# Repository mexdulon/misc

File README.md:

View this project on [CADLAB.io](https://cadlab.io/node/870). 

# misc
Miscellaneous stuff like other boards (e.g. RS485)

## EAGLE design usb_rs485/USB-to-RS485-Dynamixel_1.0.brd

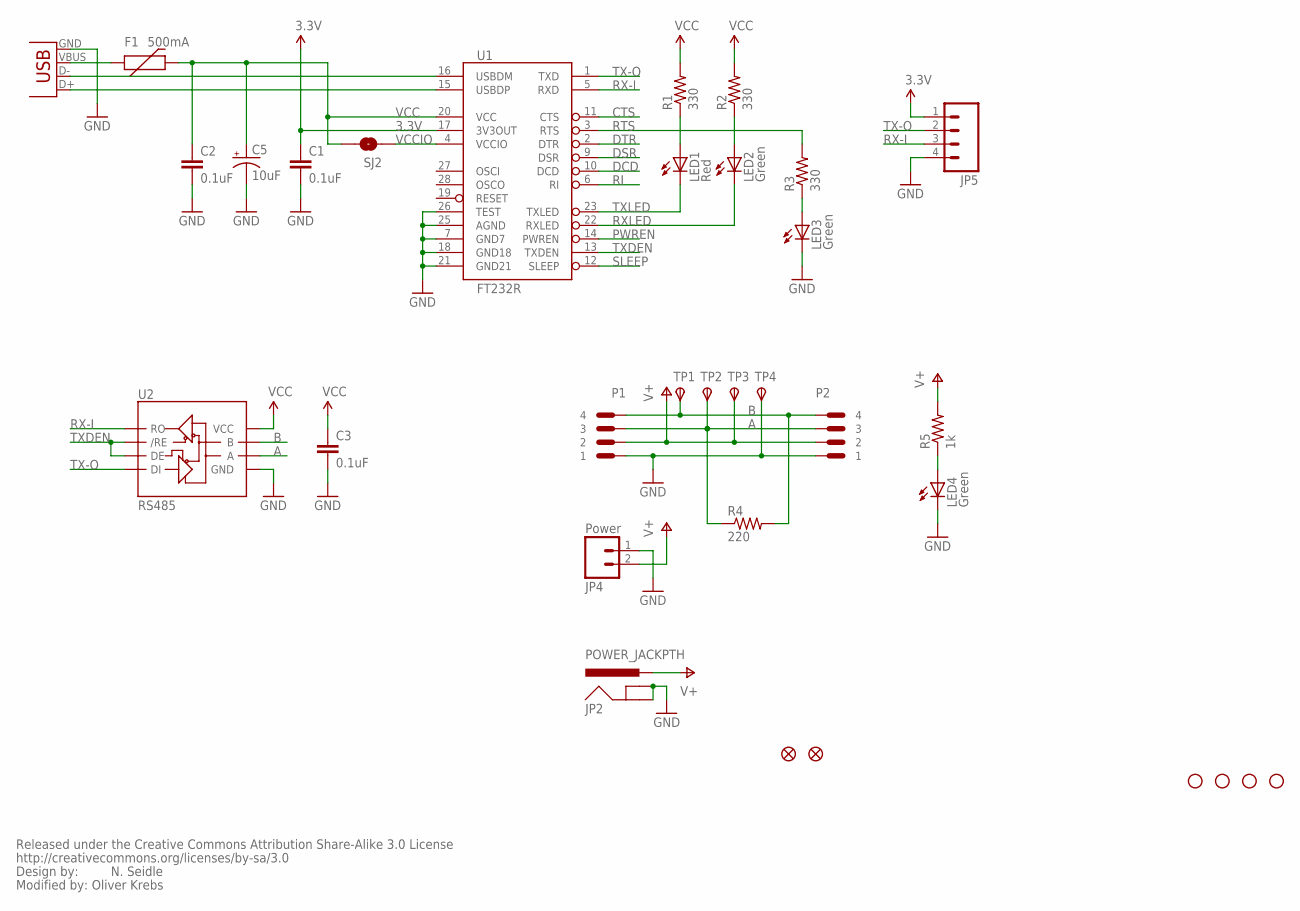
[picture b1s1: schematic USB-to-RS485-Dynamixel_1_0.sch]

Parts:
C1, C2, C3: 0.1uF; 0402-CAP
C5: 10uF; EIA3216
F1: 500mA; PTC-1206
JP1, JP6, JP7, JP8: STAND-OFF
JP2: POWER_JACKPTH; POWER_JACK_PTH
JP4: Power; 1X02_BIG_5.08
JP5: M04PTH; 1X04
JP9, JP10: FIDUCIAL1X2; FIDUCIAL-1X2
LED1: Red; LED-0603
LED2, LED3, LED4: Green; LED-0603
P1, P2: CON-4-; MOLEX-22035045
R1, R2, R3: 330; 0402-RES
R4: 220; 0402-RES
R5: 1k; 0402-RES
SJ2: SOLDERJUMPERNC2; SJ_2S-NOTRACE
TP1, TP2, TP3, TP4: TPSTP13SQ; TP13SQ
U1: FT232R; SSOP28DB
U2: RS485; SO08
U$1: CREATIVE_COMMONS
X2: USBSMD; USB-MINIB

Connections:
3.3V: C1.1, JP5.1, U1.17 (3V3OUT)
A: P1.P$3 (3), P2.P$3 (3), R4.1, TP2.TP, U2.6 (A)
B: P1.P$4 (4), P2.P$4 (4), R4.2, TP1.TP, U2.7 (B)
CTS: U1.11 (CTS)
DCD: U1.10 (DCD)
DSR: U1.9 (DSR)
DTR: U1.2 (DTR)
GND: C1.2, C2.2, C3.2, C5.C (-), JP2.GND, JP2.GNDBREAK, JP4.1, JP5.4, LED3.C, LED4.C, P1.P$1 (1), P2.P$1 (1), TP4.TP, U1.7 (GND7), U1.18 (GND18), U1.21 (GND21), U1.25 (AGND), U1.26 (TEST), U2.5 (GND), X2.GND
unnamed: LED1.A, R1.1
unnamed: LED2.A, R2.1
unnamed: F1.1, X2.VBUS
unnamed: LED3.A, R3.1
unnamed: LED4.A, R5.1
PWREN: U1.14 (PWREN)
RI: U1.6 (RI)
RTS: R3.2, U1.3 (RTS)
RX-I: JP5.3, U1.5 (RXD), U2.1 (RO)
RXLED: LED2.C, U1.22 (RXLED)
SLEEP: U1.12 (SLEEP)
TX-O: JP5.2, U1.1 (TXD), U2.4 (DI)
TXDEN: U1.13 (TXDEN), U2.2 (/RE), U2.3 (DE)
TXLED: LED1.C, U1.23 (TXLED)
USB_D+: U1.15 (USBDP), X2.D+
USB_D-: U1.16 (USBDM), X2.D-
V+: JP2.PWR, JP4.2, P1.P$2 (2), P2.P$2 (2), R5.2, TP3.TP
VCC: C2.1, C3.1, C5.A (+), F1.2, R1.2, R2.2, SJ2.2, U1.20 (VCC), U2.8 (VCC)
VCCIO: SJ2.1, U1.4 (VCCIO)

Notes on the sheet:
N. Seidle
Modified by: Oliver Krebs

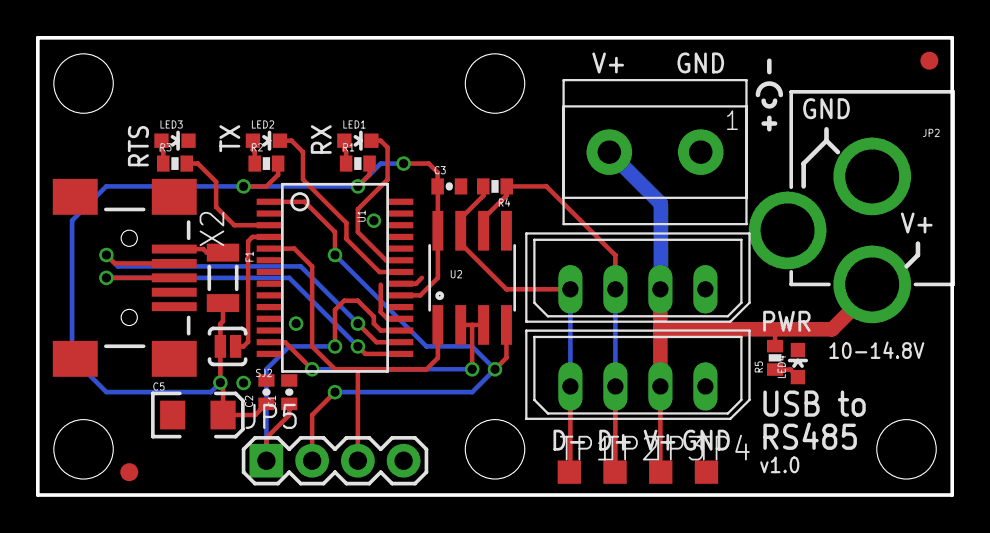
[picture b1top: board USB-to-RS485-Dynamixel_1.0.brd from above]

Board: 2 copper layers, 50.8 x 25.4 mm, 35 parts (0 on the bottom side), 20 nets.

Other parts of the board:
JP3: STAND-OFF

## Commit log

2017-01-05 +usb_rs485 dynamixel converter files upload: eagle (sch, brd), bom (csv), schematic (pdf), gerber (zip)
2017-01-05 +usb_rs485 image (jpg)
2017-01-05 *usb_rs485 board change
2017-02-07 Files renamed and layout image added Dot in file name (for version) replaced by underscore: *_1.0* -> *_1_0* Layout image for top side added (with part names and values)
2017-02-07 Files with old file name removed
2017-04-05 Update USB-to-RS485-Dynamixel_1_0.csv
    changed semicolon by comma
2017-04-05 Update USB-to-RS485-Dynamixel_1_0.csv
    corrected quote in line 9
2018-04-12 Backlink to CADLAB.io has been added.

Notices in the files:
parts and their libraries:
SparkFun: Released under the Creative Commons Attribution Share-Alike 3.0 License
SparkFun: http://creativecommons.org/licenses/by-sa/3.0
SparkFun-Connectors: Licensing: Creative Commons ShareAlike 4.0 International - https://creativecommons.org/licenses/by-sa/4.0
